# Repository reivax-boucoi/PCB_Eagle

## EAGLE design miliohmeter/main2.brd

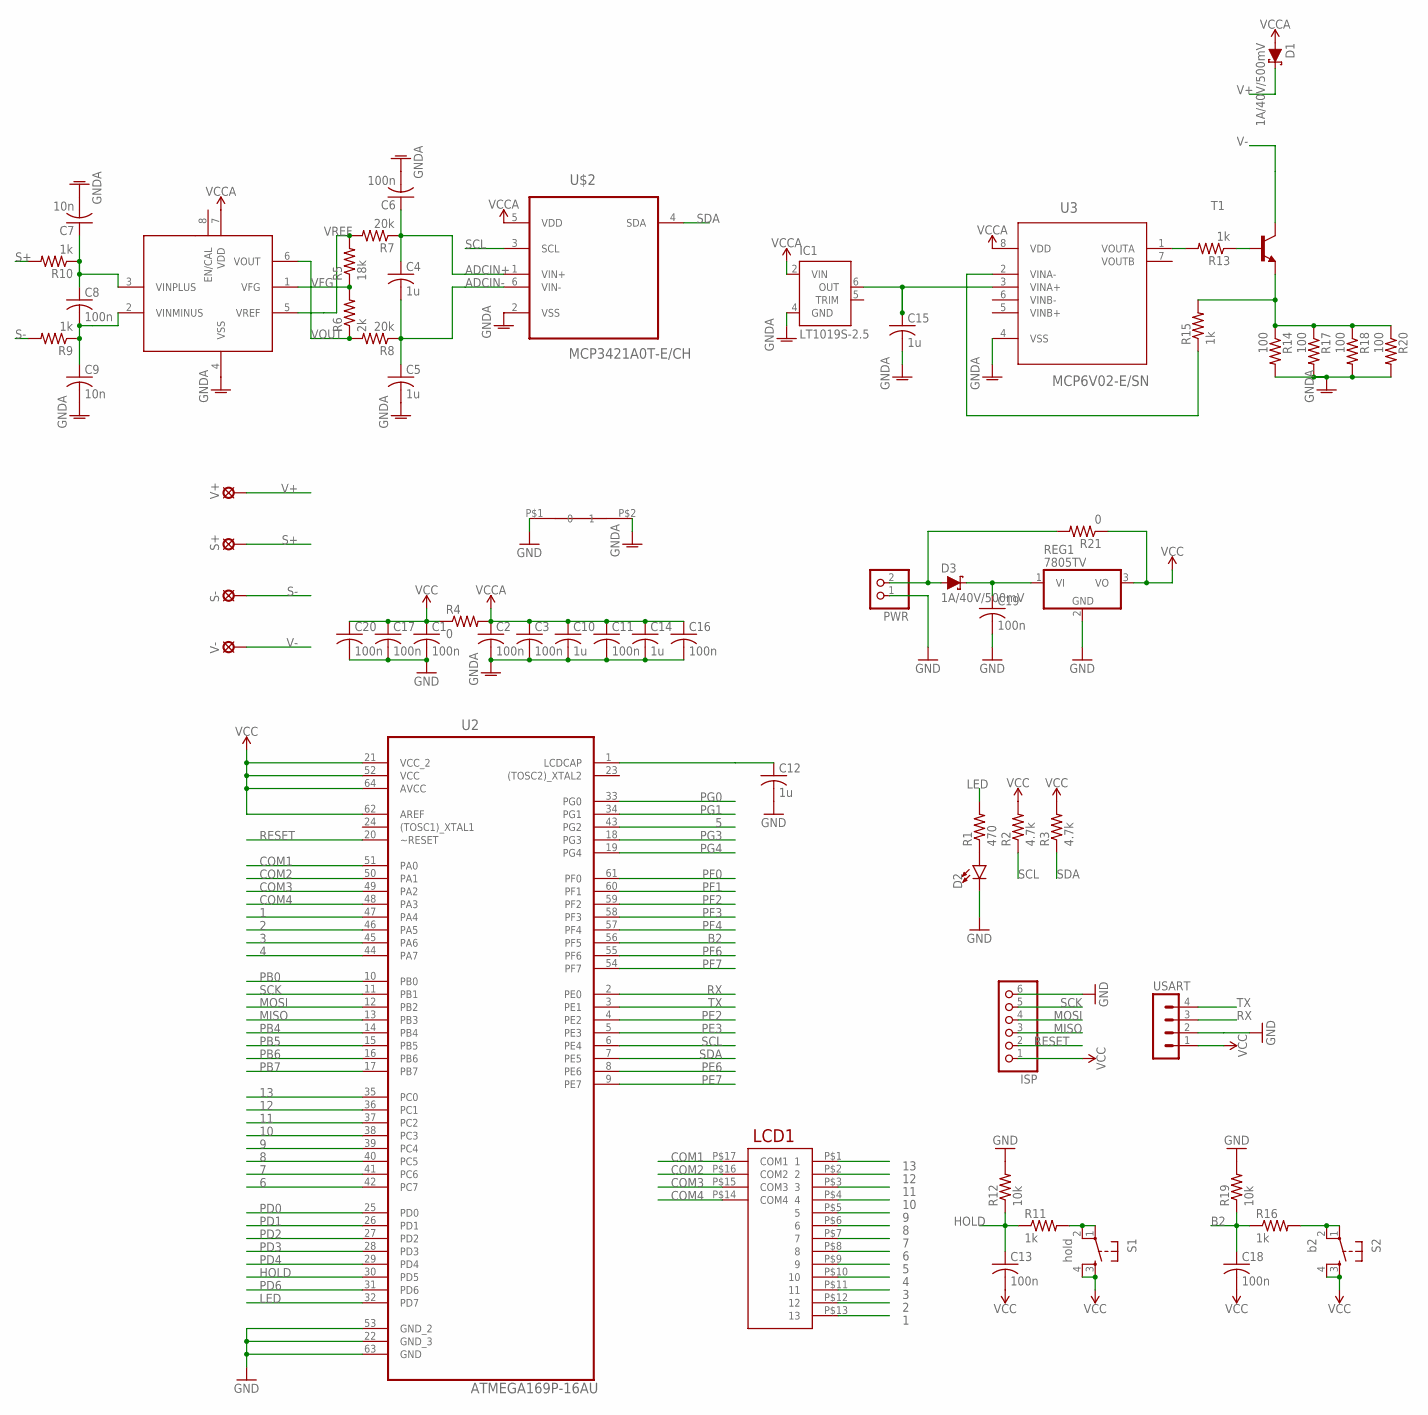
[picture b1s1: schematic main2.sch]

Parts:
C1, C2, C3, C6, C8, C11, C13, C16, C17, C18, C19, C20: 100n; C0603
C4, C5, C10, C12, C14, C15: 1u; C0603
C7, C9: 10n; C0603
D1, D3: 1A/40V/500mV; SMA-DIODE
D2: LED5MM; LED_5MM
IC1: LT1019S-2.5; SOIC8
ISP: PINHD-1X6; 1X06
LCD1: GDC0570_LCD
PWR: PINHD-1X2; 1X02
R1: 470; R0603
R2, R3: 4.7k; R0603
R4: 0; 0309/12
R5: 18k; R0603
R6: 2k; R0603
R7, R8: 20k; R0603
R9, R10, R11, R13, R15, R16: 1k; R0603
R12, R19: 10k; R0603
R14, R17, R18, R20: 100; R0603
R21: 0; R0603
REG1: 7805TV; TO220V
S1: hold; TACTILE-PTH
S2: b2; TACTILE-PTH
S+: MCS08
S-: MCS08
T1: MMBT3904LT1-NPN-SOT23-BEC; SOT23-BEC
U2: ATMEGA169P-16AU; QFP80P1600X1600X120-64N
U3: MCP6V02-E/SN; SOIC127P600X175-8N
U$2: MCP3421A0T-E/CH; SOT95P270X145-6N
U$3: MCP6N11; SOIC8
U$10: SHORT32; SHORT_32
USART: MA04-1
V+: MCS08
V-: MCS08

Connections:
1: LCD1.P$13 (13), U2.47 (PA4)
2: LCD1.P$12 (12), U2.46 (PA5)
3: LCD1.P$11 (11), U2.45 (PA6)
4: LCD1.P$10 (10), U2.44 (PA7)
5: LCD1.P$9 (9), U2.43 (PG2)
6: LCD1.P$8 (8), U2.42 (PC7)
7: LCD1.P$7 (7), U2.41 (PC6)
8: LCD1.P$6 (6), U2.40 (PC5)
9: LCD1.P$5 (5), U2.39 (PC4)
10: LCD1.P$4 (4), U2.38 (PC3)
11: LCD1.P$3 (3), U2.37 (PC2)
12: LCD1.P$2 (2), U2.36 (PC1)
13: LCD1.P$1 (1), U2.35 (PC0)
ADCIN+: C4.1, C6.1, R7.1, U$2.1 (VIN+)
ADCIN-: C4.2, C5.1, R8.1, U$2.6 (VIN-)
B2: C18.1, R16.1, R19.1, U2.56 (PF5)
COM1: LCD1.P$17 (COM1), U2.51 (PA0)
COM2: LCD1.P$16 (COM2), U2.50 (PA1)
COM3: LCD1.P$15 (COM3), U2.49 (PA2)
COM4: LCD1.P$14 (COM4), U2.48 (PA3)
GND: C1.2, C12.2, C17.2, C19.2, C20.2, D2.K (C), ISP.6, PWR.1, R12.2, R19.2, REG1.2 (GND), U2.22 (GND_3), U2.53 (GND_2), U2.63 (GND), U$10.P$1 (0), USART.2
GNDA: C2.2, C3.2, C5.2, C6.2, C7.2, C9.2, C10.2, C11.2, C14.2, C15.2, C16.2, IC1.4 (GND), R14.2, R17.2, R18.2, R20.2, U3.4 (VSS), U$2.2 (VSS), U$3.4 (VSS), U$10.P$2 (1)
HOLD: C13.1, R11.1, R12.1, U2.30 (PD5)
LCDCAP: C12.1, U2.1 (LCDCAP)
LED: R1.2, U2.32 (PD7)
MISO: ISP.3, U2.13 (PB3)
MOSI: ISP.4, U2.12 (PB2)
N2: R16.2, S2.1, S2.2
unnamed: D3.A, PWR.2, R21.2
unnamed: C15.1, IC1.6 (OUT), U3.3 (VINA+)
unnamed: R14.1, R15.2, R17.1, R18.1, R20.1, T1.E
unnamed: C8.2, C9.1, R9.1, U$3.2 (VINMINUS)
unnamed: C7.1, C8.1, R10.1, U$3.3 (VINPLUS)
unnamed: D2.A, R1.1
unnamed: R13.2, U3.1 (VOUTA)
unnamed: R13.1, T1.B
unnamed: R15.1, U3.2 (VINA-)
unnamed: R11.2, S1.1, S1.2
unnamed: C19.1, D3.C, REG1.1 (VI)
PB0: U2.10 (PB0)
PB4: U2.14 (PB4)
PB5: U2.15 (PB5)
PB6: U2.16 (PB6)
PB7: U2.17 (PB7)
PD0: U2.25 (PD0)
PD1: U2.26 (PD1)
PD2: U2.27 (PD2)
PD3: U2.28 (PD3)
PD4: U2.29 (PD4)
PD6: U2.31 (PD6)
PE2: U2.4 (PE2)
PE3: U2.5 (PE3)
PE6: U2.8 (PE6)
PE7: U2.9 (PE7)
PF0: U2.61 (PF0)
PF1: U2.60 (PF1)
PF2: U2.59 (PF2)
PF3: U2.58 (PF3)
PF4: U2.57 (PF4)
PF6: U2.55 (PF6)
PF7: U2.54 (PF7)
PG0: U2.33 (PG0)
PG1: U2.34 (PG1)
PG3: U2.18 (PG3)
PG4: U2.19 (PG4)
RESET: ISP.2, U2.20 (~RESET)
RX: U2.2 (PE0), USART.3
S+: R10.2, S+.MP
S-: R9.2, S-.MP
SCK: ISP.5, U2.11 (PB1)
SCL: R2.1, U2.6 (PE4), U$2.3 (SCL)
SDA: R3.1, U2.7 (PE5), U$2.4 (SDA)
TX: U2.3 (PE1), USART.4
V+: D1.C, V+.MP
V-: T1.C, V-.MP
VCC: C1.1, C13.2, C17.1, C18.2, C20.1, ISP.1, R2.2, R3.2, R4.1, R21.1, REG1.3 (VO), S1.3, S1.4, S2.3, S2.4, U2.21 (VCC_2), U2.52 (VCC), U2.62 (AREF), U2.64 (AVCC), USART.1
VCCA: C2.1, C3.1, C10.1, C11.1, C14.1, C16.1, D1.A, IC1.2 (VIN), R4.2, U3.8 (VDD), U$2.5 (VDD), U$3.7 (VDD)
VFG: R5.1, R6.2, U$3.1 (VFG)
VOUT: R6.1, R8.2, U$3.6 (VOUT)
VREF: R5.2, R7.2, U$3.5 (VREF)

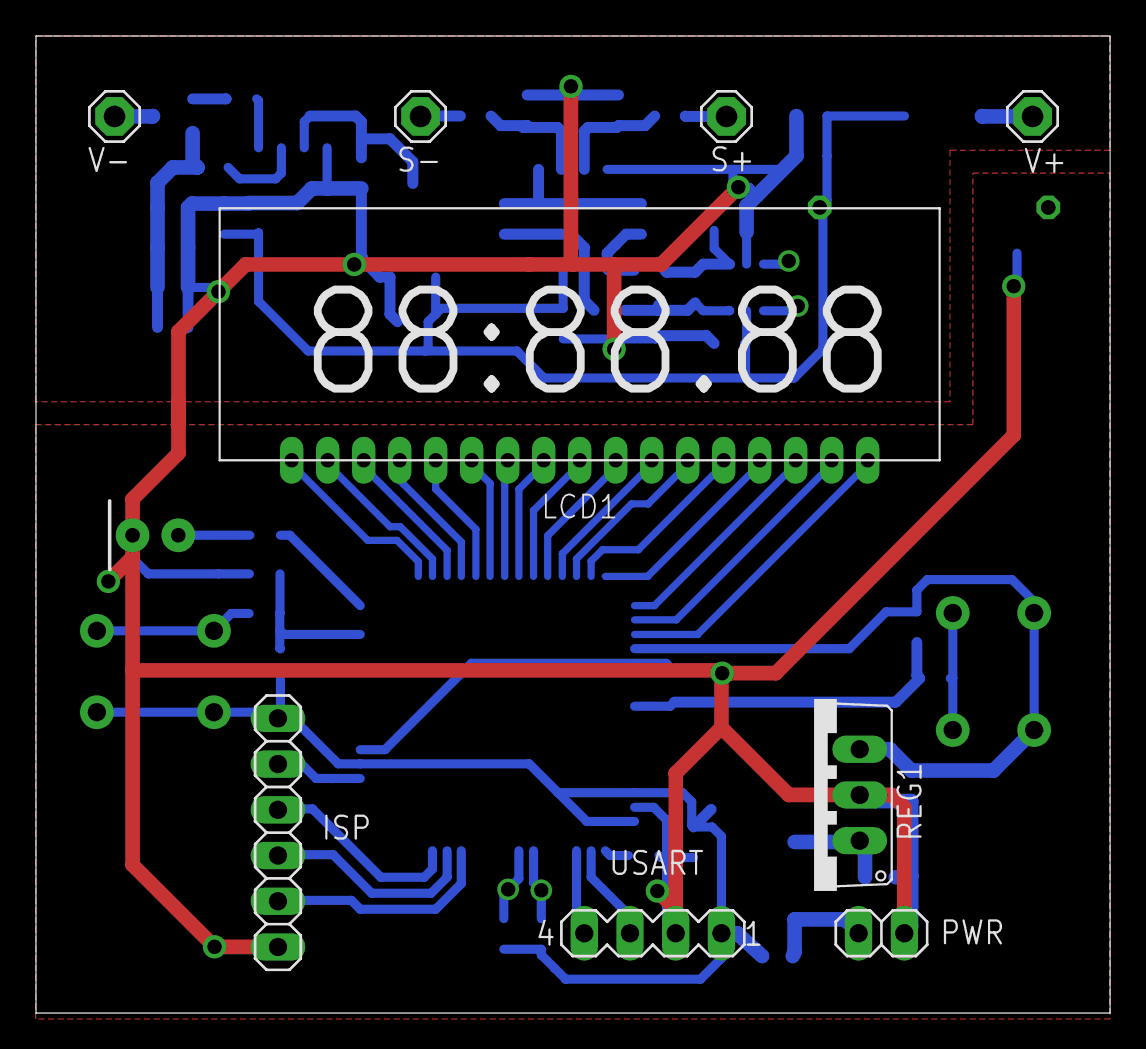
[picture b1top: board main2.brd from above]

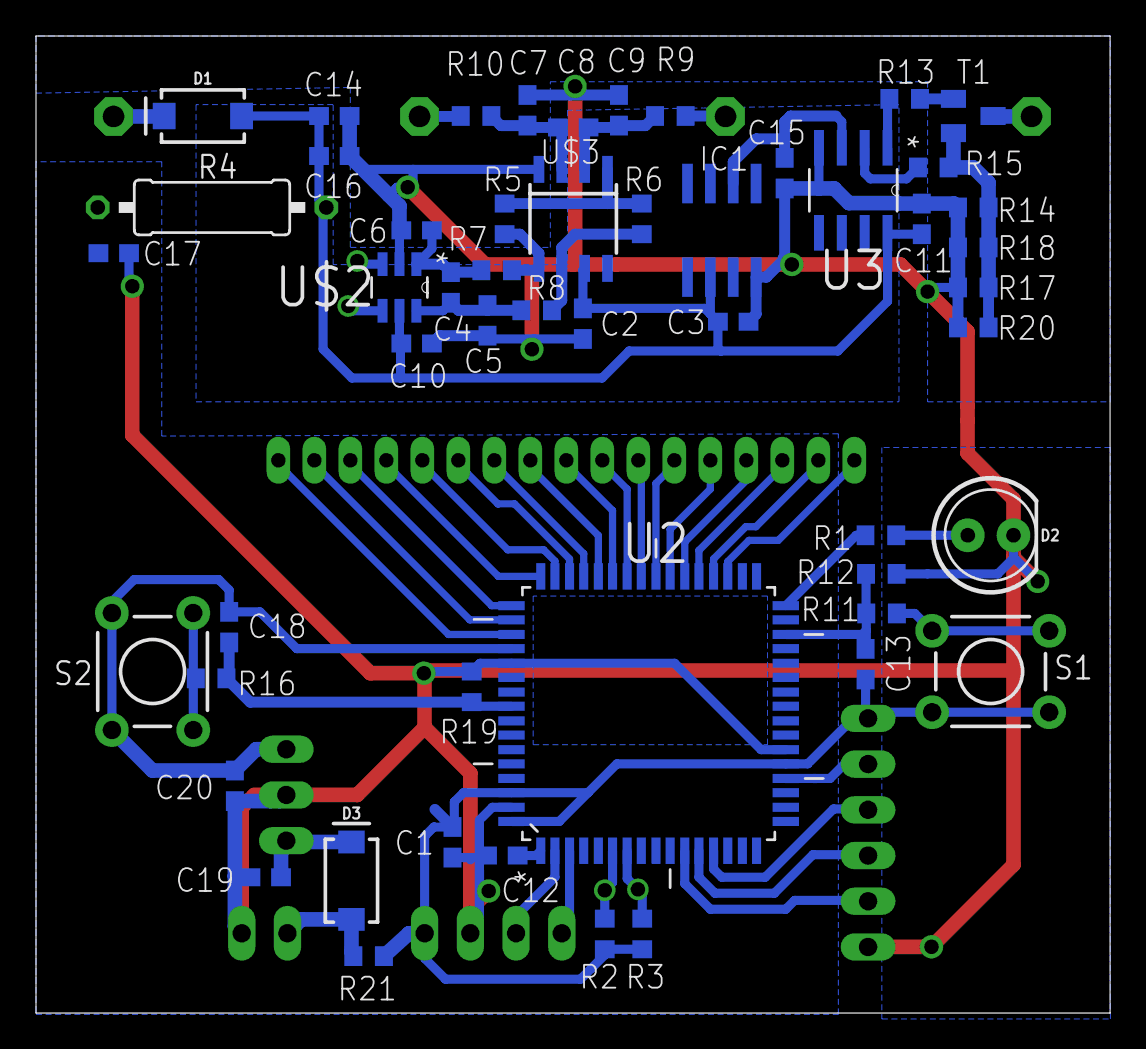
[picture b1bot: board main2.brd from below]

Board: 2 copper layers, 59.7 x 54.3 mm, 62 parts (52 on the bottom side), 54 nets.

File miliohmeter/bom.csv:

Qty;Value;Device;Parts
1;;LED5MM;D2
1;;MA04-1;USART
1;;MMBT3904LT1-NPN-SOT23-BEC;T1
1;;PINHD-1X2;PWR
1;;PINHD-1X6;ISP
1;0;R-US_0309/12;R4
1;0;R-US_R0603;R21
4;100;R-US_R0603;R14, R17, R18, R20
12;100n;C-USC0603;C1, C2, C3, C6, C8, C11, C13, C16, C17, C18, C19, C20
2;10k;R-US_R0603;R12, R19
2;10n;C-USC0603;C7, C9
1;18k;R-US_R0603;R5
2;1A/40V/500mV;DIODE-SCHOTTKY-SS14;D1, D3
6;1k;R-US_R0603;R9, R10, R11, R13, R15, R16
6;1u;C-USC0603;C4, C5, C10, C12, C14, C15
2;20k;R-US_R0603;R7, R8
1;2k;R-US_R0603;R6
2;4.7k;R-US_R0603;R2, R3
1;470;R-US_R0603;R1
1;7805TV;7805TV;REG1
1;ATMEGA169P-16AU;ATMEGA169P-16AU;U2
1;GDC0570_LCD;GDC0570_LCD;LCD1
1;LT1019S-2.5;LT1019S-2.5;IC1
1;MCP3421A0T-E/CH;MCP3421A0T-E/CH;U$2
1;MCP6N11;MCP6N11;U$3
1;MCP6V02-E/SN;MCP6V02-E/SN;U3
4;MCS08;MCS08;S+, S-, V+, V-
1;SHORT32;SHORT32;U$10
1;b2;TAC_SWITCHPTH;S2
1;hold;TAC_SWITCHPTH;S1

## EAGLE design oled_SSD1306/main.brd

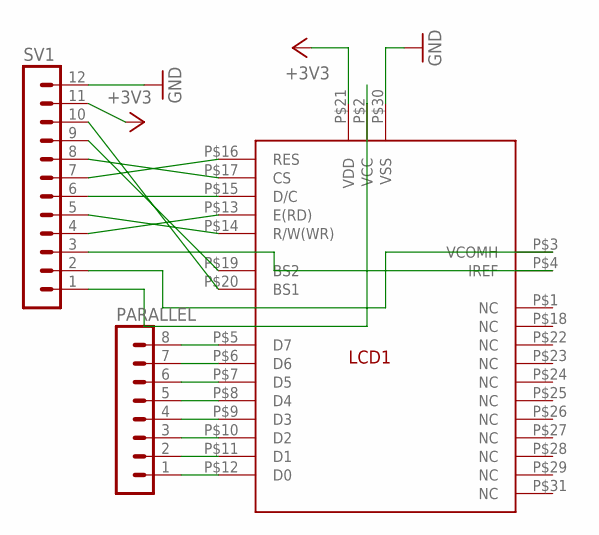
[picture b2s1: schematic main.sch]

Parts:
LCD1: SSD1306
PARALLEL: MA08-1
SV1: MA12-1

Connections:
+3V3: LCD1.P$21 (VDD), SV1.11
GND: LCD1.P$30 (VSS), SV1.12
unnamed: LCD1.P$12 (D0), PARALLEL.1
unnamed: LCD1.P$11 (D1), PARALLEL.2
unnamed: LCD1.P$10 (D2), PARALLEL.3
unnamed: LCD1.P$9 (D3), PARALLEL.4
unnamed: LCD1.P$8 (D4), PARALLEL.5
unnamed: LCD1.P$7 (D5), PARALLEL.6
unnamed: LCD1.P$6 (D6), PARALLEL.7
unnamed: LCD1.P$5 (D7), PARALLEL.8
unnamed: LCD1.P$20 (BS1), SV1.10
unnamed: LCD1.P$19 (BS2), SV1.9
unnamed: LCD1.P$14 (R/W(WR)), SV1.5
unnamed: LCD1.P$13 (E(RD)), SV1.4
unnamed: LCD1.P$15 (D/C), SV1.6
unnamed: LCD1.P$17 (CS), SV1.8
unnamed: LCD1.P$16 (RES), SV1.7
unnamed: LCD1.P$3 (VCOMH), SV1.2
unnamed: LCD1.P$4 (IREF), SV1.3
unnamed: LCD1.P$2 (VCC), SV1.1

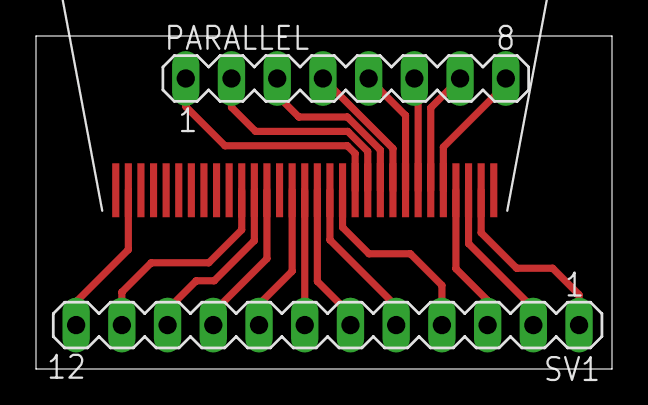
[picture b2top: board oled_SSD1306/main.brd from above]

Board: 2 copper layers, 32.0 x 18.5 mm, 3 parts (0 on the bottom side), 20 nets.

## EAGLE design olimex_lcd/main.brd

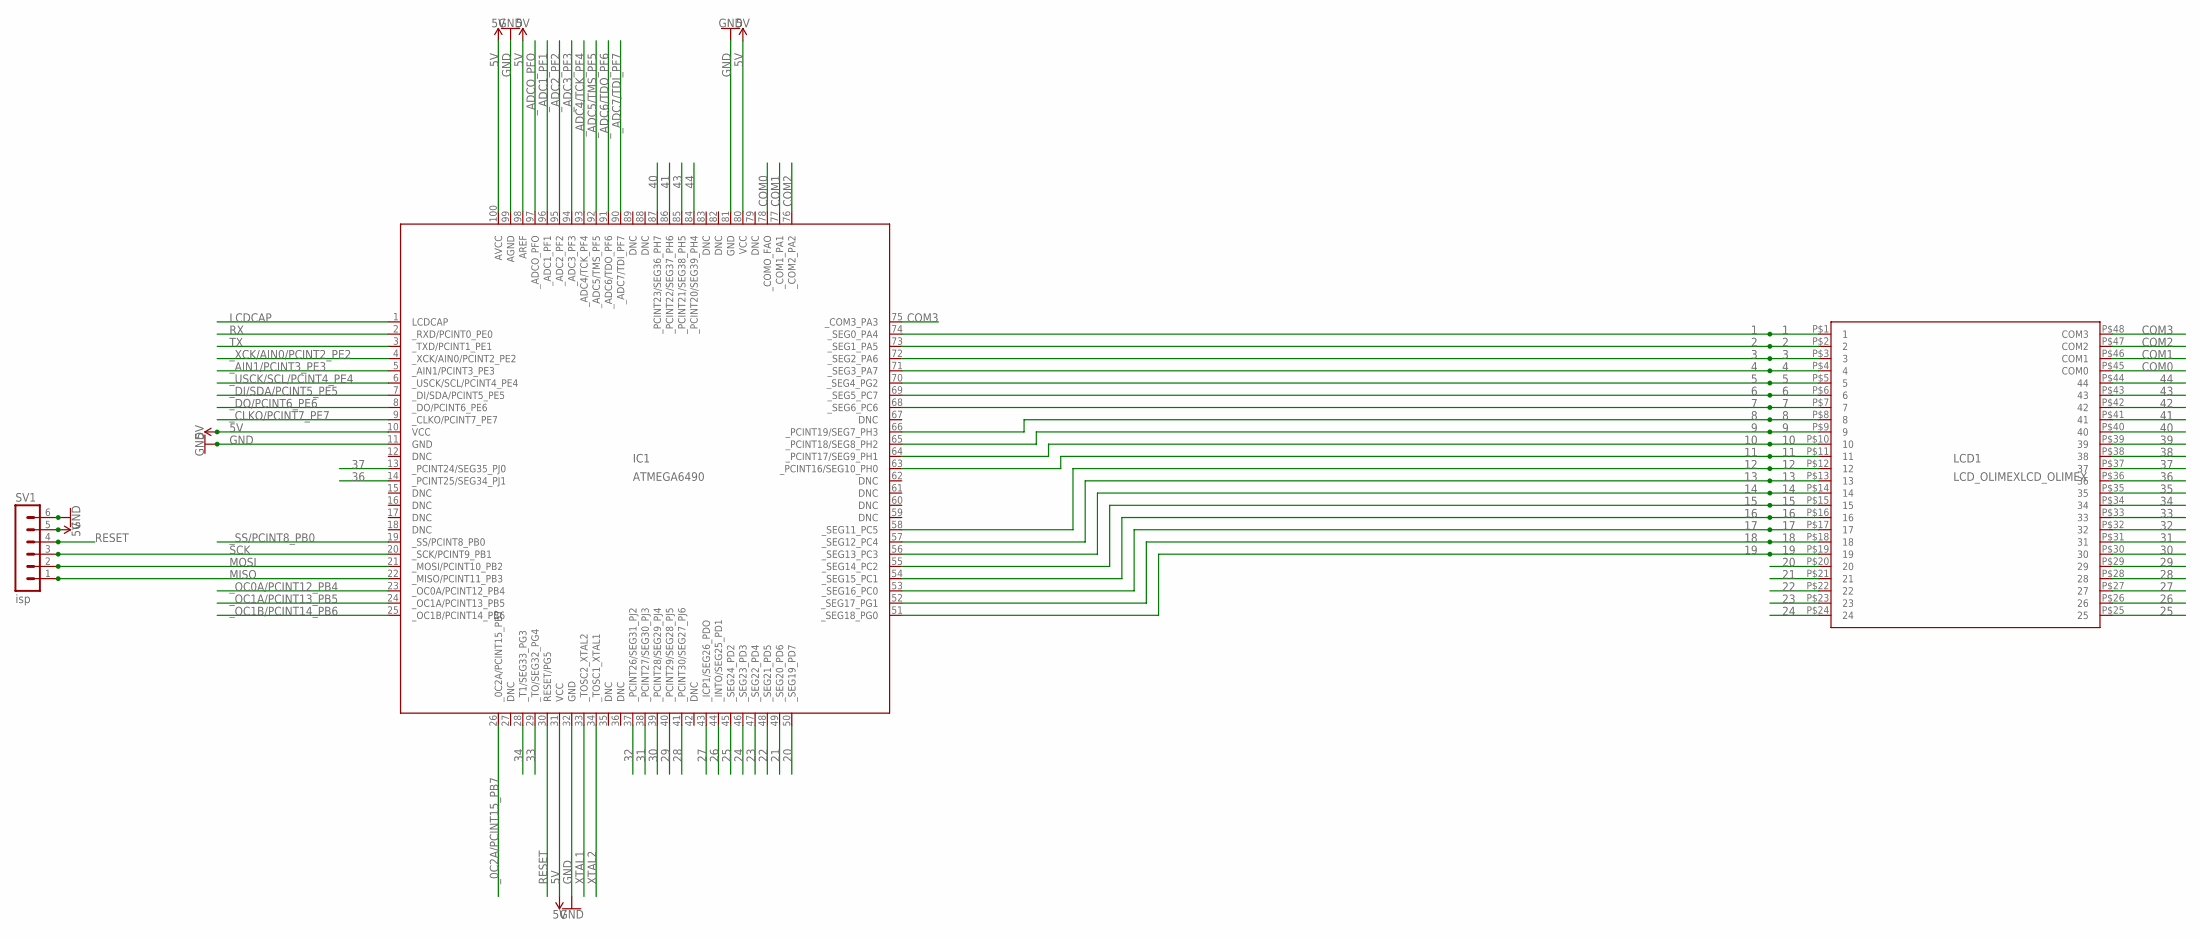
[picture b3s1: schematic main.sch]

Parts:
IC1: ATMEGA6490; TQFP100
LCD1: LCD_OLIMEXLCD_OLIMEX; LCD_OLIMEX
SV1: isp; MA06-1

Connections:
1: IC1.74 (_SEG0_PA4), LCD1.P$1 (1)
2: IC1.73 (_SEG1_PA5), LCD1.P$2 (2)
3: IC1.72 (_SEG2_PA6), LCD1.P$3 (3)
4: IC1.71 (_SEG3_PA7), LCD1.P$4 (4)
5: IC1.70 (_SEG4_PG2), LCD1.P$5 (5)
5V: IC1.10 (VCC), IC1.31 (VCC), IC1.80 (VCC), IC1.98 (AREF), IC1.100 (AVCC), SV1.5
6: IC1.69 (_SEG5_PC7), LCD1.P$6 (6)
7: IC1.68 (_SEG6_PC6), LCD1.P$7 (7)
8: IC1.66 (_PCINT19/SEG7_PH3), LCD1.P$8 (8)
9: IC1.65 (_PCINT18/SEG8_PH2), LCD1.P$9 (9)
10: IC1.64 (_PCINT17/SEG9_PH1), LCD1.P$10 (10)
11: IC1.63 (_PCINT16/SEG10_PH0), LCD1.P$11 (11)
12: IC1.58 (_SEG11_PC5), LCD1.P$12 (12)
13: IC1.57 (_SEG12_PC4), LCD1.P$13 (13)
14: IC1.56 (_SEG13_PC3), LCD1.P$14 (14)
15: IC1.55 (_SEG14_PC2), LCD1.P$15 (15)
16: IC1.54 (_SEG15_PC1), LCD1.P$16 (16)
17: IC1.53 (_SEG16_PC0), LCD1.P$17 (17)
18: IC1.52 (_SEG17_PG1), LCD1.P$18 (18)
19: IC1.51 (_SEG18_PG0), LCD1.P$19 (19)
20: IC1.50 (_SEG19_PD7), LCD1.P$20 (20)
21: IC1.49 (_SEG20_PD6), LCD1.P$21 (21)
22: IC1.48 (_SEG21_PD5), LCD1.P$22 (22)
23: IC1.47 (_SEG22_PD4), LCD1.P$23 (23)
24: IC1.46 (_SEG23_PD3), LCD1.P$24 (24)
25: IC1.45 (_SEG24_PD2), LCD1.P$25 (25)
26: IC1.44 (_INTO/SEG25_PD1), LCD1.P$26 (26)
27: IC1.43 (_ICP1/SEG26_PDO), LCD1.P$27 (27)
28: IC1.41 (_PCINT30/SEG27_PJ6), LCD1.P$28 (28)
29: IC1.40 (_PCINT29/SEG28_PJ5), LCD1.P$29 (29)
30: IC1.39 (_PCINT28/SEG29_PJ4), LCD1.P$30 (30)
31: IC1.38 (_PCINT27/SEG30_PJ3), LCD1.P$31 (31)
32: IC1.37 (_PCINT26/SEG31_PJ2), LCD1.P$32 (32)
33: IC1.29 (_TO/SEG32_PG4), LCD1.P$33 (33)
34: IC1.28 (_T1/SEG33_PG3), LCD1.P$34 (34)
35: LCD1.P$35 (35)
36: IC1.14 (_PCINT25/SEG34_PJ1), LCD1.P$36 (36)
37: IC1.13 (_PCINT24/SEG35_PJ0), LCD1.P$37 (37)
38: LCD1.P$38 (38)
39: LCD1.P$39 (39)
40: IC1.87 (_PCINT23/SEG36_PH7), LCD1.P$40 (40)
41: IC1.86 (_PCINT22/SEG37_PH6), LCD1.P$41 (41)
42: LCD1.P$42 (42)
43: IC1.85 (_PCINT21/SEG38_PH5), LCD1.P$43 (43)
44: IC1.84 (_PCINT20/SEG39_PH4), LCD1.P$44 (44)
COM0: IC1.78 (_COMO_FAO), LCD1.P$45 (COM0)
COM1: IC1.77 (_COM1_PA1), LCD1.P$46 (COM1)
COM2: IC1.76 (_COM2_PA2), LCD1.P$47 (COM2)
COM3: IC1.75 (_COM3_PA3), LCD1.P$48 (COM3)
GND: IC1.11 (GND), IC1.32 (GND), IC1.81 (GND), IC1.99 (AGND), SV1.6
LCDCAP: IC1.1 (LCDCAP)
MISO: IC1.22 (_MISO/PCINT11_PB3), SV1.1
MOSI: IC1.21 (_MOSI/PCINT10_PB2), SV1.2
RESET: IC1.30 (RESET/PG5), SV1.4
RX: IC1.2 (_RXD/PCINT0_PE0)
SCK: IC1.20 (_SCK/PCINT9_PB1), SV1.3
TX: IC1.3 (_TXD/PCINT1_PE1)
XTAL1: IC1.33 (_TOSC2_XTAL2)
XTAL2: IC1.34 (_TOSC1_XTAL1)
_0C2A/PCINT15_PB7: IC1.26 (_0C2A/PCINT15_PB7)
_ADC1_PF1: IC1.96 (_ADC1_PF1)
_ADC2_PF2: IC1.95 (_ADC2_PF2)
_ADC3_PF3: IC1.94 (_ADC3_PF3)
_ADC4/TCK_PF4: IC1.93 (_ADC4/TCK_PF4)
_ADC5/TMS_PF5: IC1.92 (_ADC5/TMS_PF5)
_ADC6/TDO_PF6: IC1.91 (_ADC6/TDO_PF6)
_ADC7/TDI_PF7: IC1.90 (_ADC7/TDI_PF7)
_ADCO_PFO: IC1.97 (_ADCO_PFO)
_AIN1/PCINT3_PE3: IC1.5 (_AIN1/PCINT3_PE3)
_CLKO/PCINT7_PE7: IC1.9 (_CLKO/PCINT7_PE7)
_DI/SDA/PCINT5_PE5: IC1.7 (_DI/SDA/PCINT5_PE5)
_DO/PCINT6_PE6: IC1.8 (_DO/PCINT6_PE6)
_OC0A/PCINT12_PB4: IC1.23 (_OC0A/PCINT12_PB4)
_OC1A/PCINT13_PB5: IC1.24 (_OC1A/PCINT13_PB5)
_OC1B/PCINT14_PB6: IC1.25 (_OC1B/PCINT14_PB6)
_SS/PCINT8_PB0: IC1.19 (_SS/PCINT8_PB0)
_USCK/SCL/PCINT4_PE4: IC1.6 (_USCK/SCL/PCINT4_PE4)
_XCK/AIN0/PCINT2_PE2: IC1.4 (_XCK/AIN0/PCINT2_PE2)

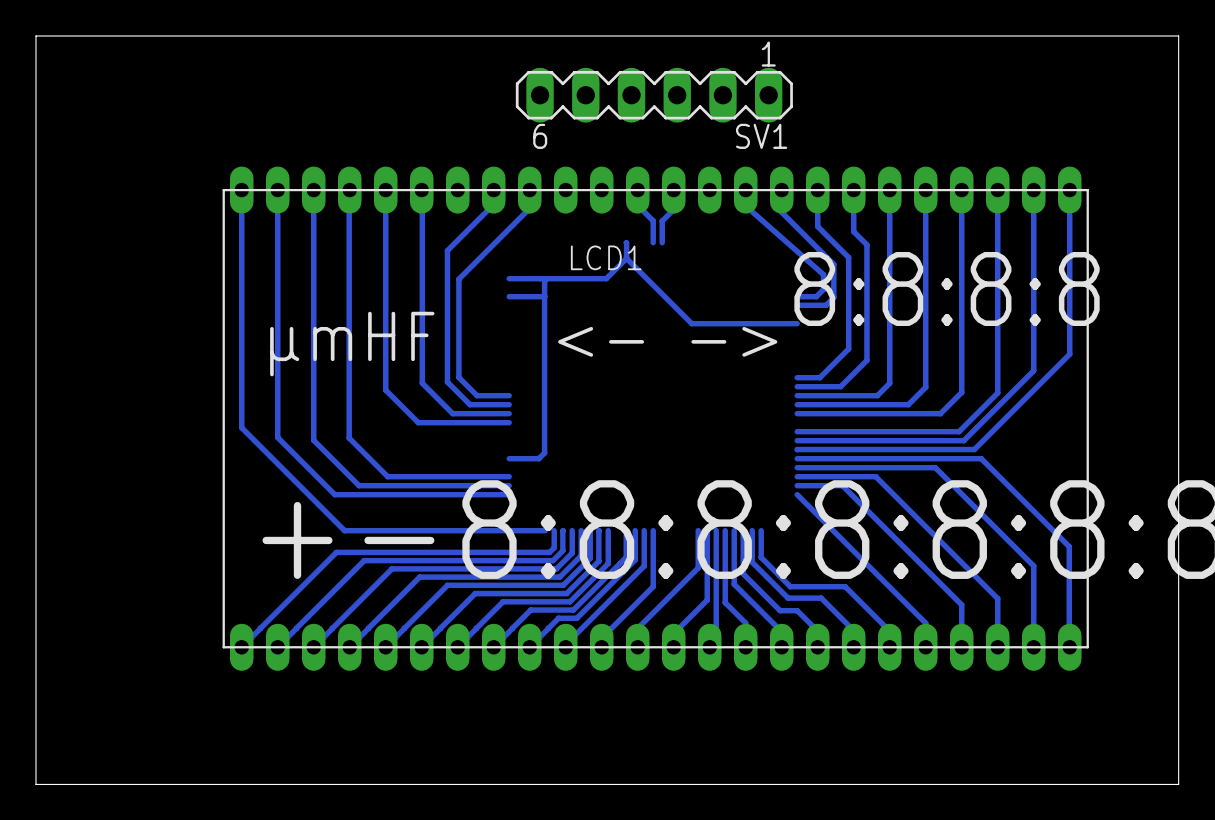
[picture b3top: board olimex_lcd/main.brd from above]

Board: 2 copper layers, 63.5 x 41.6 mm, 3 parts (1 on the bottom side), 50 nets.

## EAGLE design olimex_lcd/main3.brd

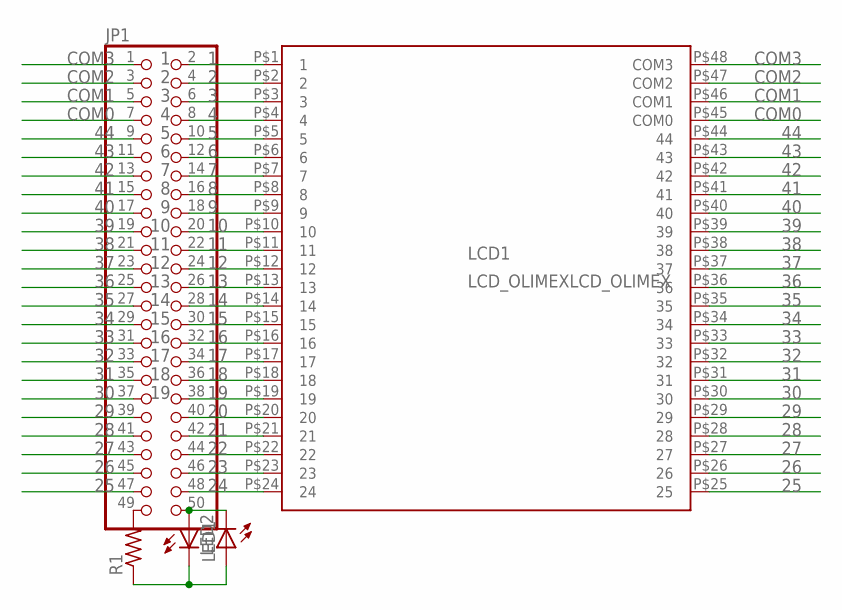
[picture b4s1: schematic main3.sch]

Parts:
JP1: PINHD-2X25; 2X25
LCD1: LCD_OLIMEXLCD_OLIMEX; LCD_OLIMEX
LED1, LED2: LED_ESML0603; LED_SML0603
R1: R-US_R0603; R0603

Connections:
1: JP1.2, LCD1.P$1 (1)
2: JP1.4, LCD1.P$2 (2)
3: JP1.6, LCD1.P$3 (3)
4: JP1.8, LCD1.P$4 (4)
5: JP1.10, LCD1.P$5 (5)
6: JP1.12, LCD1.P$6 (6)
7: JP1.14, LCD1.P$7 (7)
8: JP1.16, LCD1.P$8 (8)
9: JP1.18, LCD1.P$9 (9)
10: JP1.20, LCD1.P$10 (10)
11: JP1.22, LCD1.P$11 (11)
12: JP1.24, LCD1.P$12 (12)
13: JP1.26, LCD1.P$13 (13)
14: JP1.28, LCD1.P$14 (14)
15: JP1.30, LCD1.P$15 (15)
16: JP1.32, LCD1.P$16 (16)
17: JP1.34, LCD1.P$17 (17)
18: JP1.36, LCD1.P$18 (18)
19: JP1.38, LCD1.P$19 (19)
20: JP1.40, LCD1.P$20 (20)
21: JP1.42, LCD1.P$21 (21)
22: JP1.44, LCD1.P$22 (22)
23: JP1.46, LCD1.P$23 (23)
24: JP1.48, LCD1.P$24 (24)
25: JP1.47, LCD1.P$25 (25)
26: JP1.45, LCD1.P$26 (26)
27: JP1.43, LCD1.P$27 (27)
28: JP1.41, LCD1.P$28 (28)
29: JP1.39, LCD1.P$29 (29)
30: JP1.37, LCD1.P$30 (30)
31: JP1.35, LCD1.P$31 (31)
32: JP1.33, LCD1.P$32 (32)
33: JP1.31, LCD1.P$33 (33)
34: JP1.29, LCD1.P$34 (34)
35: JP1.27, LCD1.P$35 (35)
36: JP1.25, LCD1.P$36 (36)
37: JP1.23, LCD1.P$37 (37)
38: JP1.21, LCD1.P$38 (38)
39: JP1.19, LCD1.P$39 (39)
40: JP1.17, LCD1.P$40 (40)
41: JP1.15, LCD1.P$41 (41)
42: JP1.13, LCD1.P$42 (42)
43: JP1.11, LCD1.P$43 (43)
44: JP1.9, LCD1.P$44 (44)
COM0: JP1.7, LCD1.P$45 (COM0)
COM1: JP1.5, LCD1.P$46 (COM1)
COM2: JP1.3, LCD1.P$47 (COM2)
COM3: JP1.1, LCD1.P$48 (COM3)
unnamed: JP1.50, LED1.A, LED2.C
unnamed: JP1.49, R1.2
unnamed: LED1.C, LED2.A, R1.1

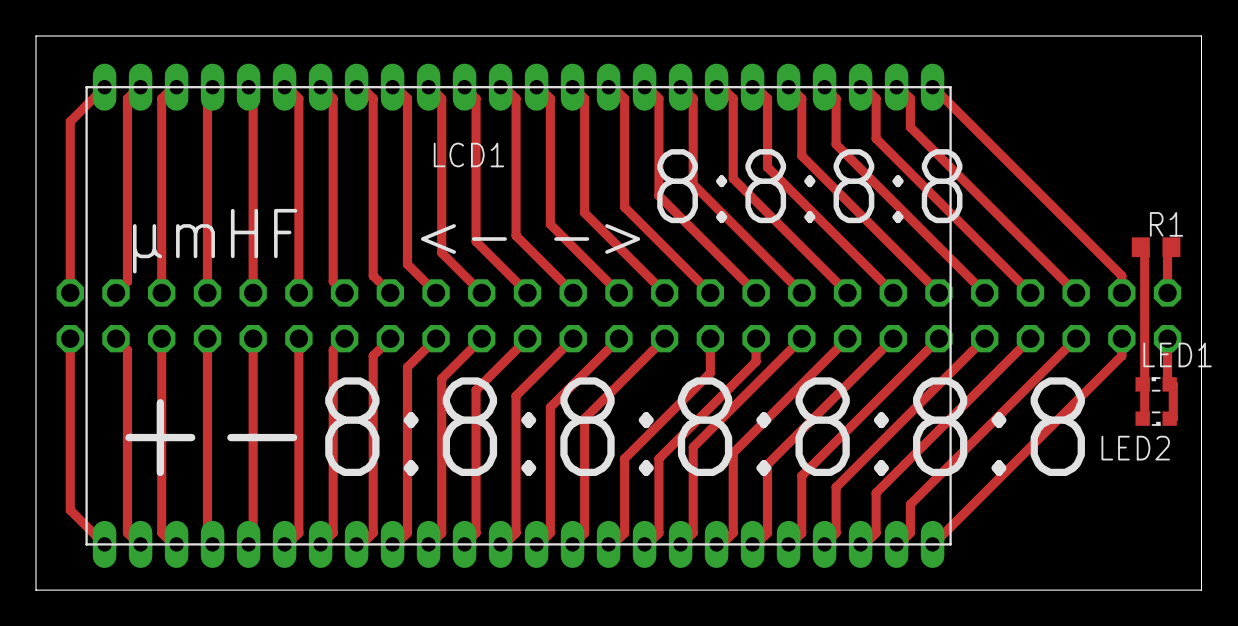
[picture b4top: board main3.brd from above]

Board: 2 copper layers, 64.8 x 30.8 mm, 5 parts (1 on the bottom side), 51 nets.

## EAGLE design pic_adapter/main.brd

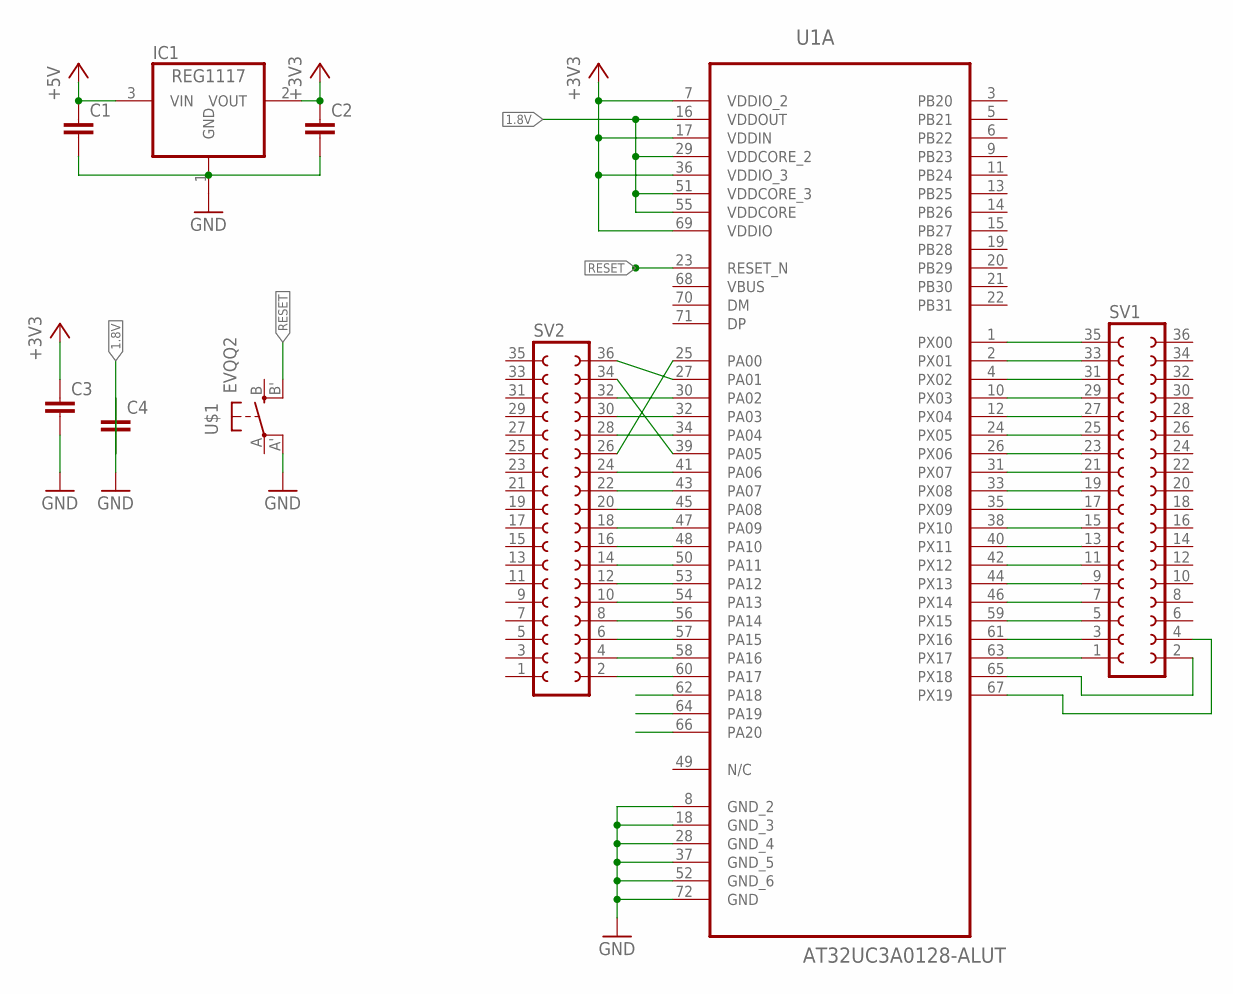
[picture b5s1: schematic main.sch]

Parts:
C1, C2, C3, C4: C-EUC0805K; C0805K
IC1: REG1117; SOT223
SV1, SV2: FE18-2
U1: AT32UC3A0128-ALUT; QFP50P2200X2200X160-144N
U$1: EVQQ2; EVQ-Q2

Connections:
1.8V: C4.2, U1.16 (VDDOUT), U1.29 (VDDCORE_2), U1.51 (VDDCORE_3), U1.55 (VDDCORE)
+3V3: C2.1, C3.1, IC1.2 (VOUT), U1.7 (VDDIO_2), U1.17 (VDDIN), U1.36 (VDDIO_3), U1.69 (VDDIO)
+5V: C1.1, IC1.3 (VIN)
GND: C3.2, C4.1, IC1.1 (GND), U1.8 (GND_2), U1.18 (GND_3), U1.28 (GND_4), U1.37 (GND_5), U1.52 (GND_6), U1.72 (GND), U$1.A' (P1)
unnamed: C1.2, C2.2
unnamed: SV1.35, U1.1 (PX00)
unnamed: SV1.33, U1.2 (PX01)
unnamed: SV1.31, U1.4 (PX02)
unnamed: SV1.29, U1.10 (PX03)
unnamed: SV1.27, U1.12 (PX04)
unnamed: SV1.25, U1.24 (PX05)
unnamed: SV1.23, U1.26 (PX06)
unnamed: SV1.21, U1.31 (PX07)
unnamed: SV1.19, U1.33 (PX08)
unnamed: SV1.17, U1.35 (PX09)
unnamed: SV1.15, U1.38 (PX10)
unnamed: SV1.13, U1.40 (PX11)
unnamed: SV1.11, U1.42 (PX12)
unnamed: SV1.9, U1.44 (PX13)
unnamed: SV1.7, U1.46 (PX14)
unnamed: SV1.5, U1.59 (PX15)
unnamed: SV1.3, U1.61 (PX16)
unnamed: SV1.1, U1.63 (PX17)
unnamed: SV2.26, U1.25 (PA00)
unnamed: SV2.36, U1.27 (PA01)
unnamed: SV2.32, U1.30 (PA02)
unnamed: SV2.30, U1.32 (PA03)
unnamed: SV2.28, U1.34 (PA04)
unnamed: SV2.34, U1.39 (PA05)
unnamed: SV2.24, U1.41 (PA06)
unnamed: SV2.22, U1.43 (PA07)
unnamed: SV2.20, U1.45 (PA08)
unnamed: SV2.18, U1.47 (PA09)
unnamed: SV2.16, U1.48 (PA10)
unnamed: SV2.14, U1.50 (PA11)
unnamed: SV2.12, U1.53 (PA12)
unnamed: SV2.10, U1.54 (PA13)
unnamed: SV2.8, U1.56 (PA14)
unnamed: SV2.6, U1.57 (PA15)
unnamed: SV2.4, U1.58 (PA16)
unnamed: SV2.2, U1.60 (PA17)
unnamed: SV1.2, U1.65 (PX18)
unnamed: SV1.4, U1.67 (PX19)
RESET: U1.23 (RESET_N), U$1.B' (S1)
VDDANA: U1.81 (VDDANA)
VDDCORE: U1.138 (VDDCORE)
VDDIO: U1.116 (VDDIO)
VDDIO_2: U1.92 (VDDIO_2)
VDDIO_3: U1.93 (VDDIO_3)
VDDIO_4: U1.108 (VDDIO_4)
VDDPLL: U1.84 (VDDPLL)

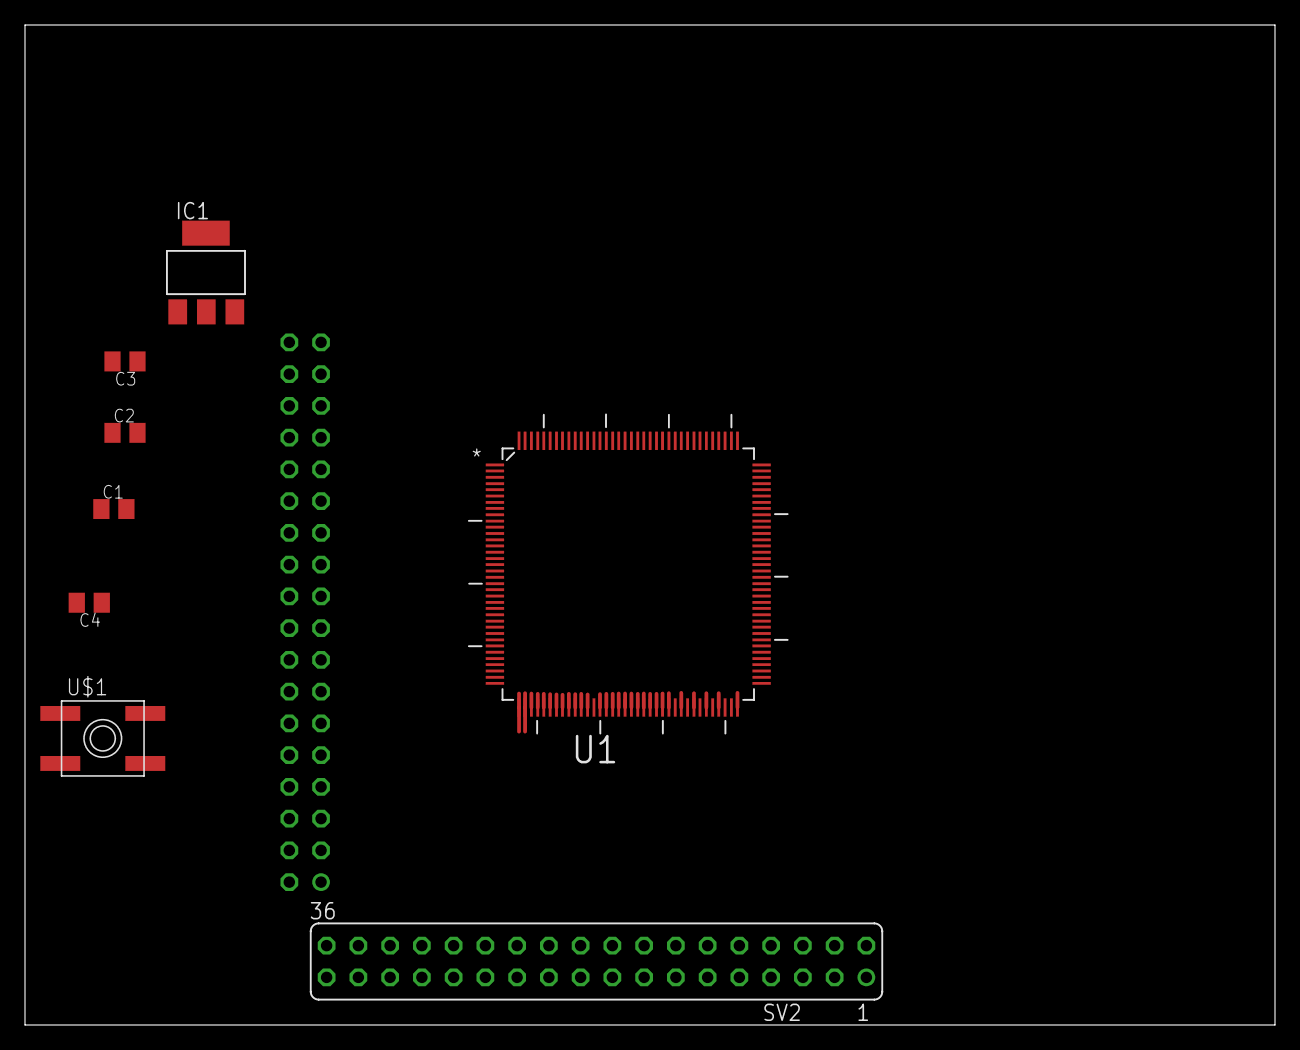
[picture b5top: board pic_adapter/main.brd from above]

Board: 2 copper layers, 100.0 x 80.0 mm, 9 parts (1 on the bottom side), 44 nets.

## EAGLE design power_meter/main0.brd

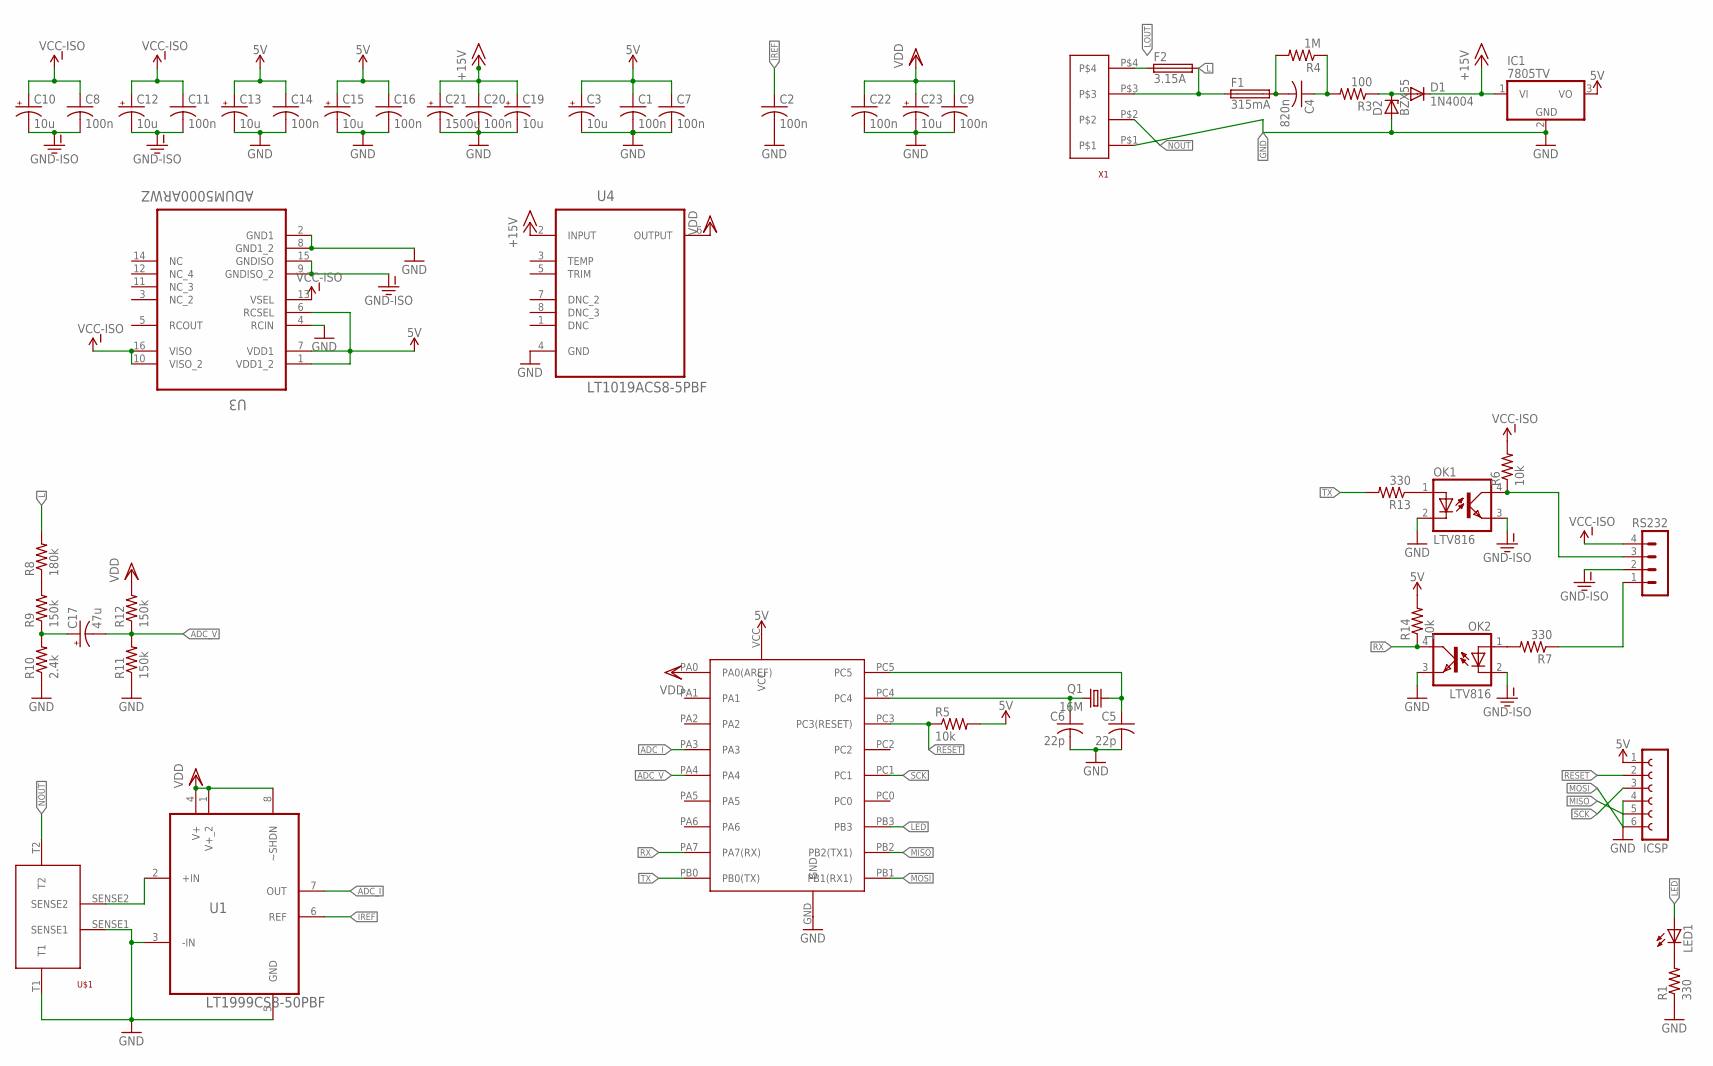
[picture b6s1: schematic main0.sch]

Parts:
C1, C2, C7, C8, C9, C11, C14, C16, C20, C22: 100n; C0805
C3, C10, C12, C13, C15, C19, C23: 10u; E2,5-5
C4: 820n; C225-087X268
C5, C6: 22p; C025-025X050
C17: 47u; E2,5-6
C21: 1500u; E3,5-10
D1: 1N4004; DO41-10
D2: BZX55; DO35Z10
F1: 315mA; SH22,5
F2: 3.15A; SH22,5
IC1: 7805TV; TO220V
ICSP: FE06-1; FE06
LED1: LEDCHIPLED_0805; CHIPLED_0805
OK1, OK2: LTV816; DIL04
Q1: 16M; HC49U-V
R1, R7, R13: 330; M0805
R3: 100; 0411/12
R4: 1M; 0309/12
R5, R6, R14: 10k; M0805
R8: 180k; 0204/7
R9: 150k; 0204/7
R10: 2.4k; 0207/10
R11, R12: 150k; M0805
RS232: MA04-1
U1: LT1999CS8-50PBF; SOIC127P600X175-8N
U3: ADUM5000ARWZ; SOIC127P1032X265-16N
U4: LT1019ACS8-5PBF; SOIC127P600X175-8N
U$1: CSR2TTE30L0F
U$8: ATTINY1634; SOIC20
X1: SCREWTERM_5MM_4WAY

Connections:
5V: C1.1, C3.+, C7.1, C13.+, C14.1, C15.+, C16.1, IC1.3 (VO), ICSP.1, R5.2, R14.2, U3.1 (VDD1_2), U3.6 (RCSEL), U3.7 (VDD1), U$8.VCC
+15V: C19.+, C20.1, C21.+, D1.C, IC1.1 (VI), U4.2 (INPUT)
ADC_I: U1.7 (OUT), U$8.PA3
ADC_V: C17.-, R11.2, R12.1, U$8.PA4
GND: C1.2, C2.2, C3.-, C5.2, C6.2, C7.2, C9.2, C13.-, C14.2, C15.-, C16.2, C19.-, C20.2, C21.-, C22.2, C23.-, D2.A, IC1.2 (GND), ICSP.4, OK1.2 (C), OK2.3 (EMIT), R1.1, R10.1, R11.1, U1.3 (-IN), U1.5 (GND), U3.2 (GND1), U3.4 (RCIN), U3.8 (GND1_2), U4.4 (GND), U$1.SENSE1, U$1.T1, U$8.GND, X1.P$1
GND-ISO: C8.2, C10.-, C11.2, C12.-, OK1.3 (EMIT), OK2.2 (C), RS232.2, U3.9 (GNDISO_2), U3.15 (GNDISO)
IREF: C2.1, U1.6 (REF)
L: F1.1, F2.2, R8.2, X1.P$3
LED: LED1.A, U$8.PB3
LOUT: F2.1, X1.P$4
MISO: ICSP.5, U$8.PB2 (PB2(TX1))
MOSI: ICSP.6, U$8.PB1 (PB1(RX1))
unnamed: C4.1, R3.2, R4.1
unnamed: C4.2, F1.2, R4.2
unnamed: D1.A, D2.C, R3.1
unnamed: U1.2 (+IN), U$1.SENSE2
unnamed: OK1.4 (COL), R6.1, RS232.3
unnamed: C5.1, Q1.1, U$8.PC5
unnamed: LED1.C, R1.2
unnamed: C6.1, Q1.2, U$8.PC4
unnamed: OK2.1 (A), R7.2
unnamed: R7.1, RS232.1
unnamed: R8.1, R9.2
unnamed: C17.+, R9.1, R10.2
unnamed: OK1.1 (A), R13.1
NOUT: U$1.T2, X1.P$2
RESET: ICSP.2, R5.1, U$8.PC3 (PC3(RESET))
RX: OK2.4 (COL), R14.1, U$8.PA7 (PA7(RX))
SCK: ICSP.3, U$8.PC1
TX: R13.2, U$8.PB0 (PB0(TX))
VCC-ISO: C8.1, C10.+, C11.1, C12.+, R6.2, RS232.4, U3.10 (VISO_2), U3.13 (VSEL), U3.16 (VISO)
VDD: C9.1, C22.1, C23.+, R12.2, U1.1 (V+_2), U1.4 (V+), U1.8 (~SHDN), U4.6 (OUTPUT), U$8.PA0 (PA0(AREF))

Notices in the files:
parts and their libraries:
SparkFun-PowerSymbols: Licensing: Creative Commons ShareAlike 4.0 International - https://creativecommons.org/licenses/by-sa/4.0
